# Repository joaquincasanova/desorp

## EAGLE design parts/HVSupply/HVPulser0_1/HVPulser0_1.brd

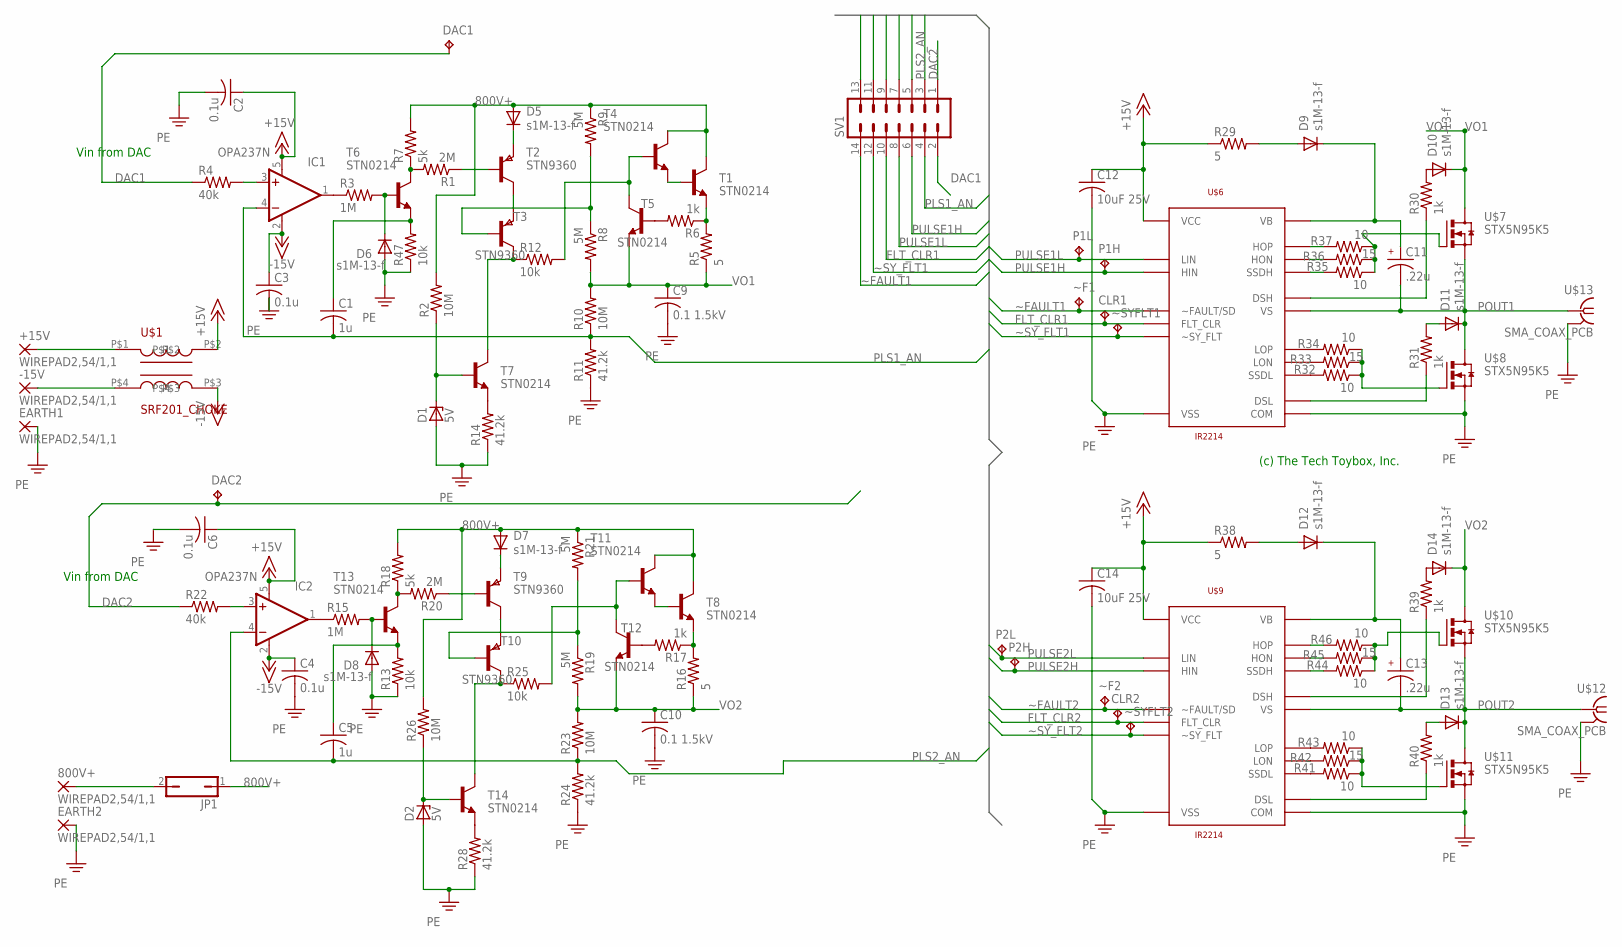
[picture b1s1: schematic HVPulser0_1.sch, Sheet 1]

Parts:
800V+: WIREPAD2,54/1,1; 2,54/1,1
+15V: WIREPAD2,54/1,1; 2,54/1,1
-15V: WIREPAD2,54/1,1; 2,54/1,1
C1, C5: 1u; C0805
C2, C3, C4, C6: 0.1u; C0805
C9, C10: 0.1 1.5kV; C2225K
C11, C13: .22u; C050-035X075; PARTNO C1608X7R1H224K080AB
C12, C14: 10uF 25V; C0805
CLR1, CLR2: TPTP10R; TP10R
D1, D2: 5V; DO41Z10
D5, D6, D7, D8, D9, D10, D11, D12, D13, D14: s1M-13-f; DO214AC
DAC1, DAC2: TPTP10R; TP10R
EARTH1, EARTH2: WIREPAD2,54/1,1; 2,54/1,1
IC1, IC2: OPA237N; SOT23-5
JP1: JP1Q; JP1
P1H, P1L, P2H, P2L: TPTP10R; TP10R
R1, R20: 2M; P0613/15
R2, R10, R23, R26: 10M; P0613/15
R3, R15: 1M; R0603
R4, R22: 40k; R0603
R5, R16: 5; P0613/15
R6, R17: 1k; P0613/15
R7, R18: 5k; R0603
R8, R9, R19, R21: 5M; P0613/15
R11, R14, R24, R28: 41.2k; P0613/15
R12, R25: 10k; R0603
R13, R47: 10k; R0805
R29, R38: 5; 0207/10
R30, R31, R39, R40: 1k; R0603
R32, R34, R35, R37, R41, R43, R44, R46: 10; R0805
R33, R36, R42, R45: 15; R0805
SV1: MA07-2
T1, T4, T5, T6, T7, T8, T11, T12, T13, T14: STN0214; SOT223
T2, T3, T9, T10: STN9360; SOT223
U$1: SRF201_CHOKE; CHOKE_BOURNES_SRF2012
U$6, U$9: IR2214; SSOP24-IR-0.65
U$7, U$8, U$10, U$11: STX5N95K5; TO220AV
U$12, U$13: SMA_COAX_PCB; SMA-COAX-V-TECONNECT
~F1, ~F2: TPTP10R; TP10R
~SYFLT1, ~SYFLT2: TPTP10R; TP10R

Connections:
800V+: D5.A, D7.A, JP1.1, R2.2, R7.2, R9.1, R18.2, R21.1, R26.2, T1.4 (C), T4.4 (C), T8.4 (C), T11.4 (C)
+15V: C2.1, C6.1, C12.1, C14.1, IC1.5 (V+), IC2.5 (V+), R29.1, R38.1, U$1.P$2, U$6.P$11 (VCC), U$9.P$11 (VCC)
+800VIN: 800V+.1, JP1.2
-15V: C3.1, C4.1, IC1.2 (V-), IC2.2 (V-), U$1.P$3
DAC1: DAC1.TP, R4.1, SV1.2
DAC2: DAC2.TP, R22.1, SV1.1
FLT_CLR1: CLR1.TP, SV1.10, U$6.P$3 (FLT_CLR)
FLT_CLR2: CLR2.TP, SV1.9, U$9.P$3 (FLT_CLR)
unnamed: -15V.1, U$1.P$4
unnamed: +15V.1, U$1.P$1
unnamed: C1.1, R47.2, T6.3 (E)
unnamed: C5.1, R13.2, T13.3 (E)
unnamed: D9.A, R29.2
unnamed: R31.1, U$6.P$12 (DSL)
unnamed: D11.A, R31.2
unnamed: R32.1, R33.1, R34.1, U$8.1 (G)
unnamed: R35.1, R36.1, R37.1, U$7.1 (G)
unnamed: R30.1, U$6.P$24 (DSH)
unnamed: D10.A, R30.2
unnamed: D12.A, R38.2
unnamed: R41.2, U$9.P$7 (SSDL)
unnamed: R42.2, U$9.P$9 (LON)
unnamed: R43.2, U$9.P$10 (LOP)
unnamed: IC1.1 (OUT), R3.1
unnamed: T2.2 (C), T2.4 (C), T3.3 (E)
unnamed: R1.1, T2.1 (B)
unnamed: D5.C, T2.3 (E)
unnamed: D6.C, R3.2, T6.1 (B)
unnamed: IC1.3 (+IN), R4.2
unnamed: R40.1, U$9.P$12 (DSL)
unnamed: R5.2, R6.1, T1.3 (E)
unnamed: T1.1 (B), T4.3 (E)
unnamed: R12.2, T4.1 (B), T5.4 (C)
unnamed: R6.2, T5.1 (B)
unnamed: R8.1, R9.2, T3.1 (B)
unnamed: R1.2, R7.1, T6.4 (C)
unnamed: R12.1, T3.2 (C), T3.4 (C), T7.4 (C)
unnamed: R14.2, T7.3 (E)
unnamed: IC2.1 (OUT), R15.1
unnamed: D1.C, R2.1, T7.1 (B)
unnamed: T9.2 (C), T9.4 (C), T10.3 (E)
unnamed: R16.2, R17.1, T8.3 (E)
unnamed: T8.1 (B), T11.3 (E)
unnamed: R17.2, T12.1 (B)
unnamed: R19.1, R21.2, T10.1 (B)
unnamed: R20.1, T9.1 (B)
unnamed: D7.C, T9.3 (E)
unnamed: R25.2, T11.1 (B), T12.4 (C)
unnamed: D8.C, R15.2, T13.1 (B)
unnamed: R18.1, R20.2, T13.4 (C)
unnamed: D13.A, R40.2
unnamed: IC2.3 (+IN), R22.2
unnamed: R25.1, T10.2 (C), T10.4 (C), T14.4 (C)
unnamed: R28.2, T14.3 (E)
unnamed: D2.C, R26.1, T14.1 (B)
unnamed: R32.2, U$6.P$7 (SSDL)
unnamed: R33.2, U$6.P$9 (LON)
unnamed: R34.2, U$6.P$10 (LOP)
unnamed: R41.1, R42.1, R43.1, U$11.1 (G)
unnamed: R44.1, R45.1, R46.1, U$10.1 (G)
unnamed: R39.1, U$9.P$24 (DSH)
unnamed: D14.A, R39.2
unnamed: R46.2, U$9.P$21 (HOP)
unnamed: R45.2, U$9.P$20 (HON)
unnamed: R44.2, U$9.P$18 (SSDH)
unnamed: R37.2, U$6.P$21 (HOP)
unnamed: R36.2, U$6.P$20 (HON)
unnamed: R35.2, U$6.P$18 (SSDH)
PE: C2.2, C3.2, C4.2, C6.2, C9.2, C10.2, C12.2, C14.2, D1.A, D2.A, D6.A, D8.A, EARTH1.1, EARTH2.1, R11.1, R13.1, R14.1, R24.1, R28.1, R47.1, U$6.P$6 (VSS), U$6.P$8 (COM), U$8.3 (S), U$9.P$6 (VSS), U$9.P$8 (COM), U$11.3 (S), U$12.2, U$12.3 (2), U$12.4 (2), U$12.5 (2), U$13.2, U$13.3 (2), U$13.4 (2), U$13.5 (2)
PLS1_AN: C1.2, IC1.4 (-IN), R10.1, R11.2, SV1.4
PLS2_AN: C5.2, IC2.4 (-IN), R23.1, R24.2, SV1.3
POUT1: C11.2, D11.C, U$6.P$19 (VS), U$7.3 (S), U$8.2 (D), U$13.1
POUT2: C13.2, D13.C, U$9.P$19 (VS), U$10.3 (S), U$11.2 (D), U$12.1
PULSE1H: P1H.TP, SV1.6, U$6.P$1 (HIN)
PULSE1L: P1L.TP, SV1.8, U$6.P$2 (LIN)
PULSE2H: P2H.TP, SV1.13, U$9.P$1 (HIN)
PULSE2L: P2L.TP, SV1.11, U$9.P$2 (LIN)
VB3: C11.1, D9.C, U$6.P$23 (VB)
VB4: C13.1, D12.C, U$9.P$23 (VB)
VO1: C9.1, D10.C, R5.1, R8.2, R10.2, T5.3 (E), U$7.2 (D)
VO2: C10.1, D14.C, R16.1, R19.2, R23.2, T12.3 (E), U$10.2 (D)
~FAULT1: SV1.14, U$6.P$5 (~FAULT/SD), ~F1.TP
~FAULT2: SV1.5, U$9.P$5 (~FAULT/SD), ~F2.TP
~SY_FLT1: SV1.12, U$6.P$4 (~SY_FLT), ~SYFLT1.TP
~SY_FLT2: SV1.7, U$9.P$4 (~SY_FLT), ~SYFLT2.TP

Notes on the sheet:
Vin from DAC
(c) The Tech Toybox, Inc.

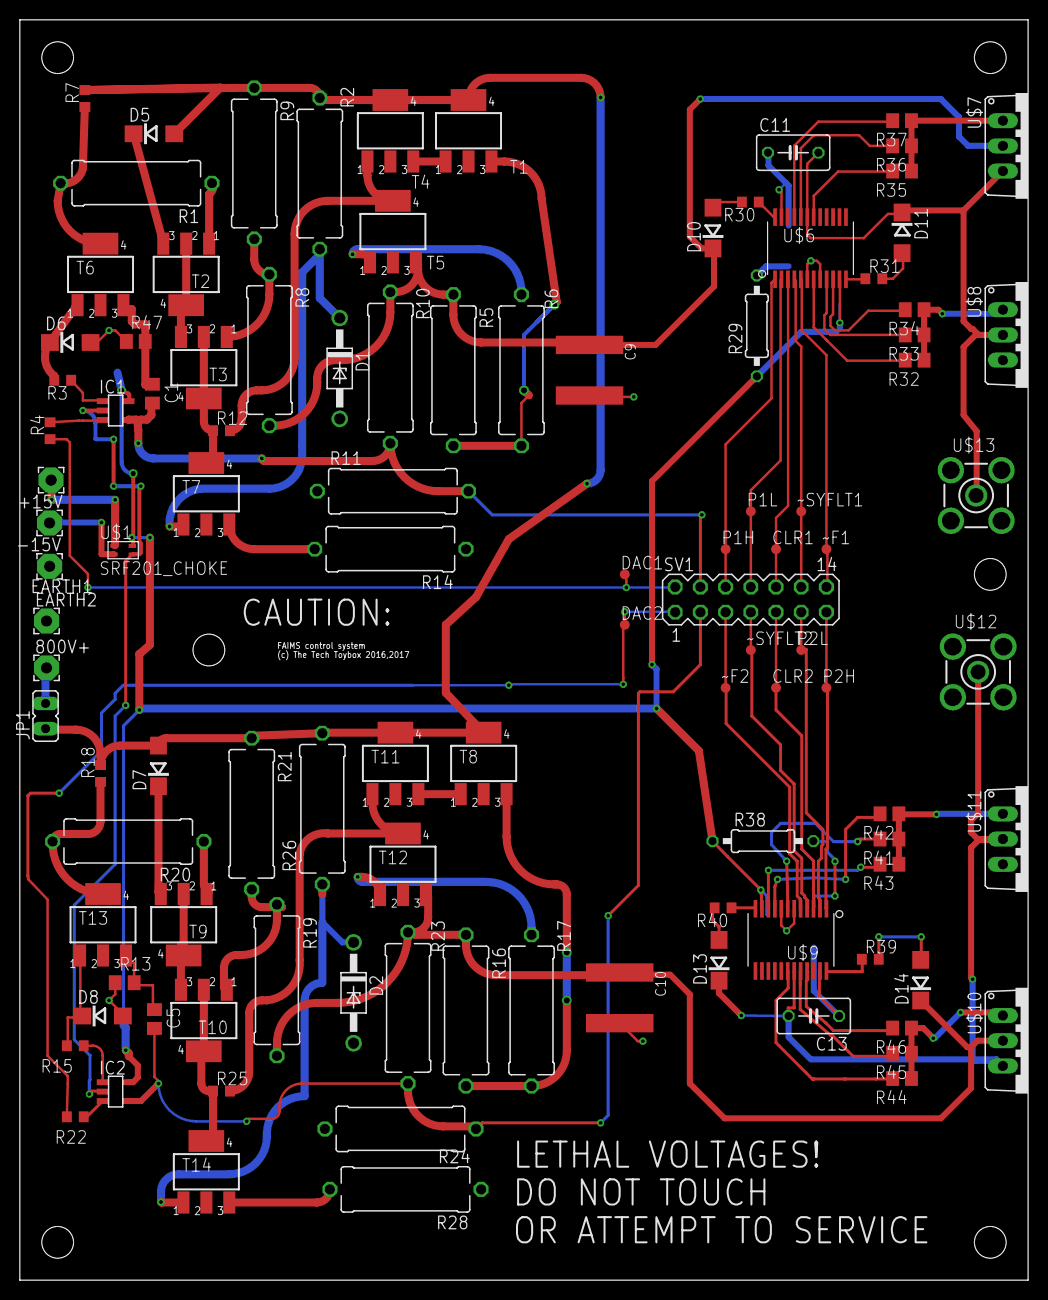
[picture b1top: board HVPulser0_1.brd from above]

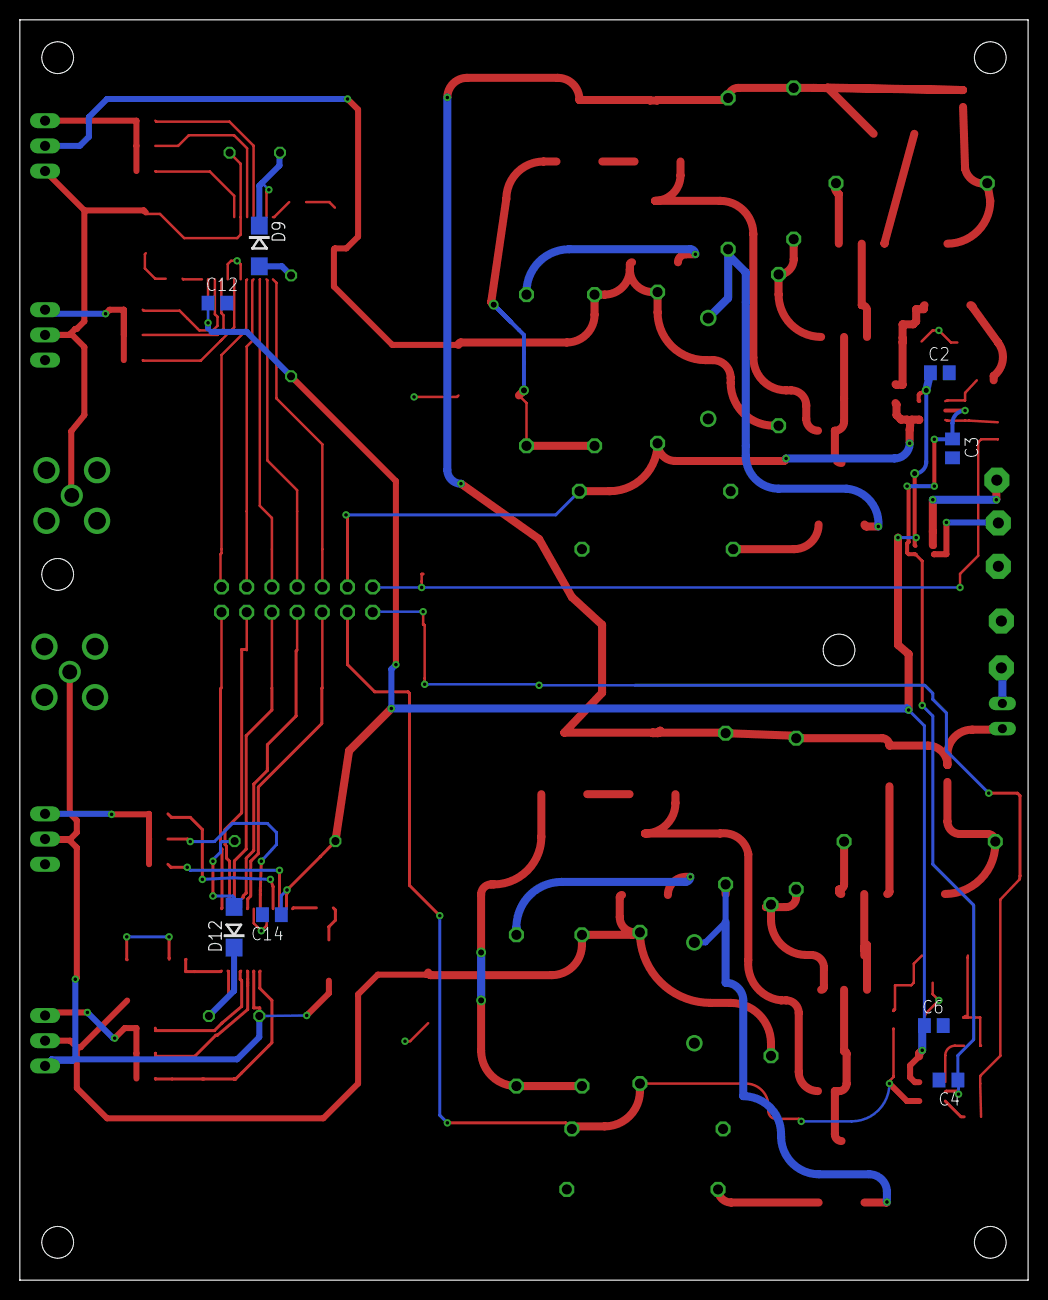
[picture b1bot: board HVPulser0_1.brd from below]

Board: 2 copper layers, 101.6 x 127.0 mm, 114 parts (8 on the bottom side), 85 nets.

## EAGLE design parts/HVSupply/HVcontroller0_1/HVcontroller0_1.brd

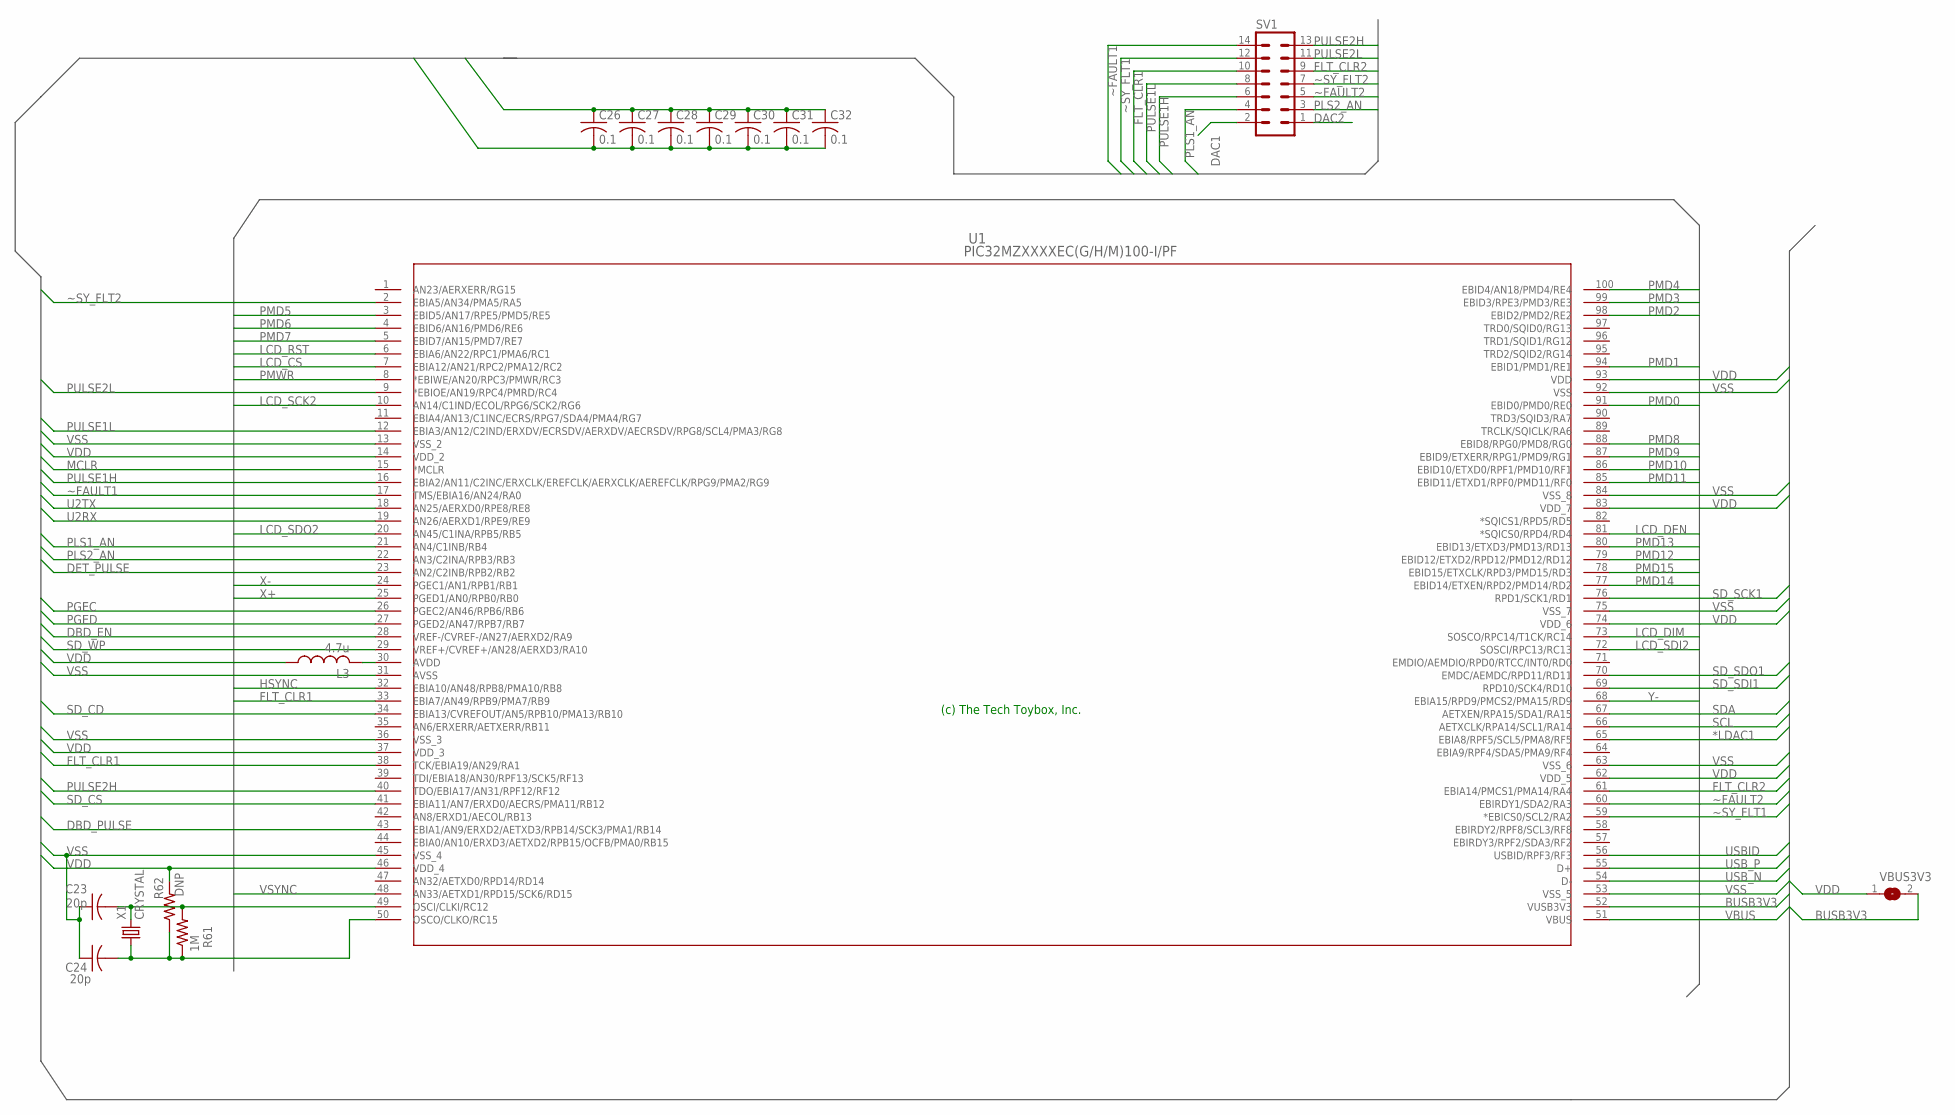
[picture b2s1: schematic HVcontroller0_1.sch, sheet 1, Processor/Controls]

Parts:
C23, C24: 20p; C0402
C26, C27, C28, C29, C30, C31, C32: 0.1; C0603
L3: 4.7u; L2012C
R61: 1M; R0402
R62: DNP; R0402
SV1: MA07-2
U1: PIC32MZXXXXEC(G/H/M)100-I/PF; TQFP100_14X14MC
VBUS3V3: SJ
X1: CRYSTAL; ABM

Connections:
*LDAC1: U1.65 (EBIA8/RPF5/SCL5/PMA8/RF5); also elsewhere on the board
BUSB3V3: U1.52 (VUSB3V3), VBUS3V3.2
DAC1: SV1.2; also elsewhere on the board
DAC2: SV1.1; also elsewhere on the board
DBD_EN: U1.28 (VREF-/CVREF-/AN27/AERXD2/RA9)
DBD_PULSE: U1.43 (EBIA1/AN9/ERXD2/AETXD3/RPB14/SCK3/PMA1/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)
DET_PULSE: U1.23 (AN2/C2INB/RPB2/RB2); also elsewhere on the board
FLT_CLR1: SV1.10, U1.38 (TCK/EBIA19/AN29/RA1)
FLT_CLR2: SV1.9, U1.61 (EBIA14/PMCS1/PMA14/RA4)
HSYNC: U1.32 (EBIA10/AN48/RPB8/PMA10/RB8)
LCD_CS: U1.7 (EBIA12/AN21/RPC2/PMA12/RC2)
LCD_DEN: U1.81 (*SQICS0/RPD4/RD4)
LCD_DIM: U1.73 (SOSCO/RPC14/T1CK/RC14)
LCD_RST: U1.6 (EBIA6/AN22/RPC1/PMA6/RC1)
LCD_SCK2: U1.10 (AN14/C1IND/ECOL/RPG6/SCK2/RG6)
LCD_SDI2: U1.72 (SOSCI/RPC13/RC13)
LCD_SDO2: U1.20 (AN45/C1INA/RPB5/RB5)
MCLR: U1.15 (*MCLR); also elsewhere on the board
unnamed: L3.2, U1.30 (AVDD)
unnamed: C23.2, R61.2, U1.49 (OSCI/CLKI/RC12), X1.P$2 (2)
unnamed: C24.2, R61.1, R62.1, U1.50 (OSCO/CLKO/RC15), X1.P$1 (1)
PGEC: U1.26 (PGEC2/AN46/RPB6/RB6); also elsewhere on the board
PGED: U1.27 (PGED2/AN47/RPB7/RB7); also elsewhere on the board
PLS1_AN: SV1.4, U1.21 (AN4/C1INB/RB4)
PLS2_AN: SV1.3, U1.22 (AN3/C2INA/RPB3/RB3)
PMD0: U1.91 (EBID0/PMD0/RE0)
PMD1: U1.94 (EBID1/PMD1/RE1)
PMD2: U1.98 (EBID2/PMD2/RE2)
PMD3: U1.99 (EBID3/RPE3/PMD3/RE3)
PMD4: U1.100 (EBID4/AN18/PMD4/RE4)
PMD5: U1.3 (EBID5/AN17/RPE5/PMD5/RE5)
PMD6: U1.4 (EBID6/AN16/PMD6/RE6)
PMD7: U1.5 (EBID7/AN15/PMD7/RE7)
PMD8: U1.88 (EBID8/RPG0/PMD8/RG0)
PMD9: U1.87 (EBID9/ETXERR/RPG1/PMD9/RG1)
PMD10: U1.86 (EBID10/ETXD0/RPF1/PMD10/RF1)
PMD11: U1.85 (EBID11/ETXD1/RPF0/PMD11/RF0)
PMD12: U1.79 (EBID12/ETXD2/RPD12/PMD12/RD12)
PMD13: U1.80 (EBID13/ETXD3/PMD13/RD13)
PMD14: U1.77 (EBID14/ETXEN/RPD2/PMD14/RD2)
PMD15: U1.78 (EBID15/ETXCLK/RPD3/PMD15/RD3)
PMWR: U1.8 (*EBIWE/AN20/RPC3/PMWR/RC3)
PULSE1H: SV1.6, U1.16 (EBIA2/AN11/C2INC/ERXCLK/EREFCLK/AERXCLK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)
PULSE1L: SV1.8, U1.12 (EBIA3/AN12/C2IND/ERXDV/ECRSDV/AERXDV/AE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)
PULSE2H: SV1.13, U1.40 (TDO/EBIA17/AN31/RPF12/RF12)
PULSE2L: SV1.11, U1.9 (*EBIOE/AN19/RPC4/PMRD/RC4)
SCL: U1.66 (AETXCLK/RPA14/SCL1/RA14); also elsewhere on the board
SDA: U1.67 (AETXEN/RPA15/SDA1/RA15); also elsewhere on the board
SD_CD: U1.34 (EBIA13/CVREFOUT/AN5/RPB10/PMA13/RB10); also elsewhere on the board
SD_CS: U1.41 (EBIA11/AN7/ERXD0/AECRS/PMA11/RB12); also elsewhere on the board
SD_SCK1: U1.76 (RPD1/SCK1/RD1); also elsewhere on the board
SD_SDI1: U1.69 (RPD10/SCK4/RD10); also elsewhere on the board
SD_SDO1: U1.70 (EMDC/AEMDC/RPD11/RD11); also elsewhere on the board
SD_WP: U1.29 (VREF+/CVREF+/AN28/AERXD3/RA10); also elsewhere on the board
U2RX: U1.19 (AN26/AERXD1/RPE9/RE9); also elsewhere on the board
U2TX: U1.18 (AN25/AERXD0/RPE8/RE8); also elsewhere on the board
USBID: U1.56 (USBID/RPF3/RF3); also elsewhere on the board
USB_N: U1.54 (D-); also elsewhere on the board
USB_P: U1.55 (D+); also elsewhere on the board
VBUS: U1.51 (VBUS); also elsewhere on the board
VDD: C26.1, C27.1, C28.1, C29.1, C30.1, C31.1, C32.1, L3.1, R62.2, U1.14 (VDD_2), U1.37 (VDD_3), U1.46 (VDD_4), U1.62 (VDD_5), U1.74 (VDD_6), U1.83 (VDD_7), U1.93 (VDD), VBUS3V3.1; also elsewhere on the board
VSS: C23.1, C24.1, C26.2, C27.2, C28.2, C29.2, C30.2, C31.2, C32.2, U1.13 (VSS_2), U1.31 (AVSS), U1.36 (VSS_3), U1.45 (VSS_4), U1.53 (VSS_5), U1.63 (VSS_6), U1.75 (VSS_7), U1.84 (VSS_8), U1.92 (VSS); also elsewhere on the board
VSYNC: U1.48 (AN33/AETXD1/RPD15/SCK6/RD15)
X+: U1.25 (PGED1/AN0/RPB0/RB0)
X-: U1.24 (PGEC1/AN1/RPB1/RB1)
Y+: U1.33 (EBIA7/AN49/RPB9/PMA7/RB9)
Y-: U1.68 (EBIA15/RPD9/PMCS2/PMA15/RD9)
~FAULT1: SV1.14, U1.17 (TMS/EBIA16/AN24/RA0)
~FAULT2: SV1.5, U1.60 (EBIRDY1/SDA2/RA3)
~SY_FLT1: SV1.12, U1.59 (*EBICS0/SCL2/RA2)
~SY_FLT2: SV1.7, U1.2 (EBIA5/AN34/PMA5/RA5)

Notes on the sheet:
(c) The Tech Toybox, Inc.

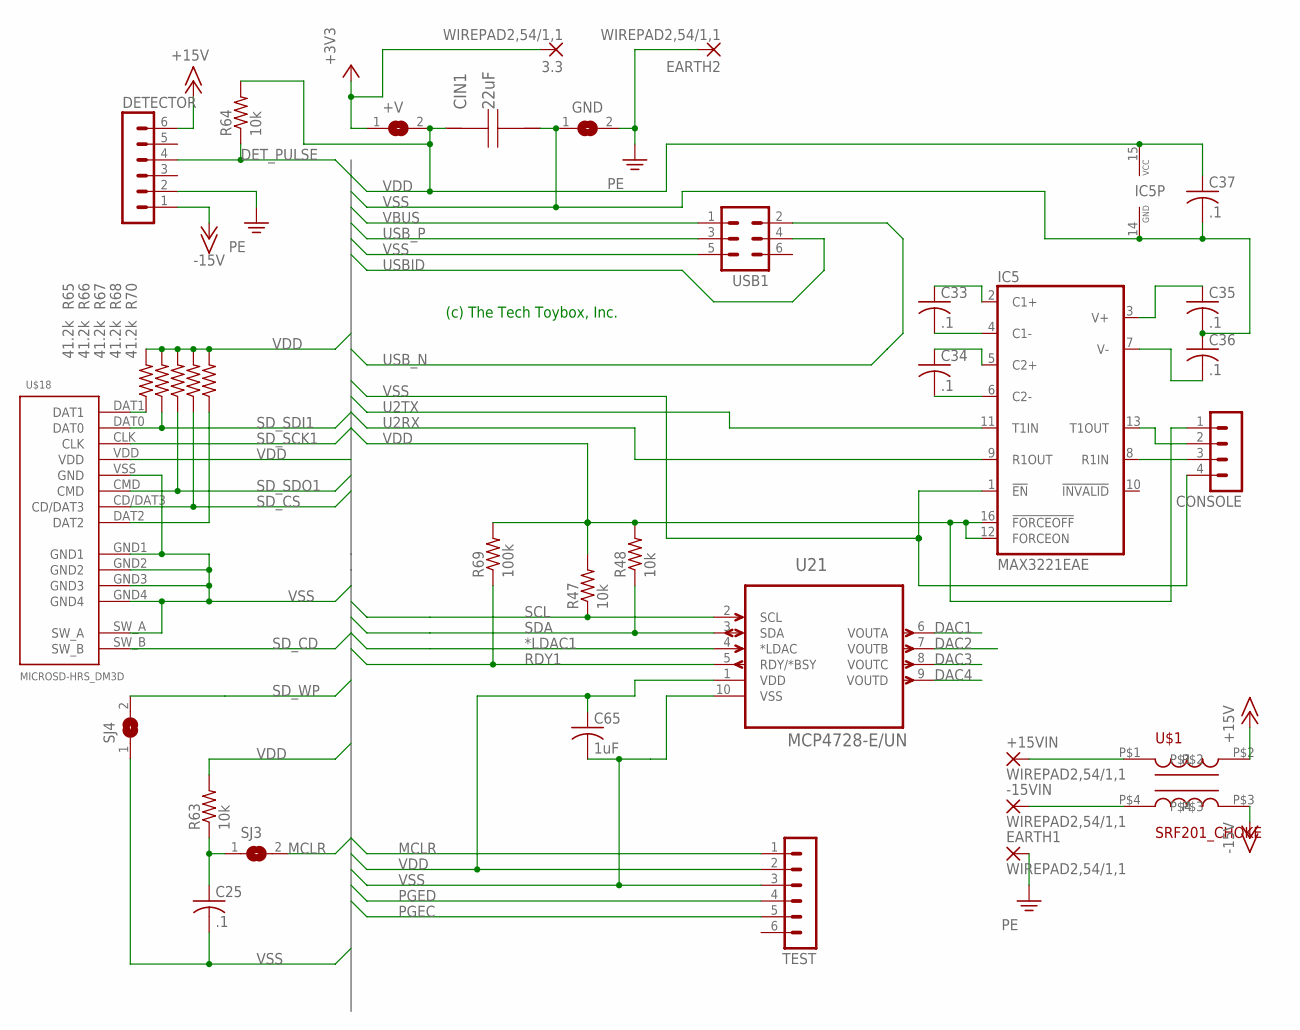
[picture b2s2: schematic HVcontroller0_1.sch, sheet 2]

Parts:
3.3: WIREPAD2,54/1,1; 2,54/1,1
+15VIN: WIREPAD2,54/1,1; 2,54/1,1
+V: SJW
-15VIN: WIREPAD2,54/1,1; 2,54/1,1
C25, C33, C34, C35, C36, C37: .1; C0402
C65: 1uF; C0402
CIN1: 22uF; 1210
CONSOLE: MA04-1
DETECTOR: MA06-1
EARTH1, EARTH2: WIREPAD2,54/1,1; 2,54/1,1
GND: SJW
IC5: MAX3221EAE; SSOP16
R47, R48, R63, R64: 10k; R0805
R65, R66, R67, R68, R70: 41.2k; R0603
R69: 100k; R0805
SJ3, SJ4: SJ
TEST: MA06-1
U21: MCP4728-E/UN; SOP50P490X110-10N
U$1: SRF201_CHOKE; CHOKE_BOURNES_SRF2012
U$18: MICROSD-HRS_DM3D; DM3D
USB1: MA03-2

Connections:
*LDAC1: U21.4 (*LDAC); also elsewhere on the board
+3V3: 3.3.1, +V.1
+15V: DETECTOR.6, U$1.P$2
-15V: DETECTOR.1, U$1.P$3
DAC1: U21.6 (VOUTA); also elsewhere on the board
DAC2: U21.7 (VOUTB); also elsewhere on the board
DAC3: U21.8 (VOUTC)
DAC4: U21.9 (VOUTD)
DET_PULSE: DETECTOR.4, R64.1; also elsewhere on the board
MCLR: SJ3.2, TEST.1; also elsewhere on the board
unnamed: -15VIN.1, U$1.P$4
unnamed: +15VIN.1, U$1.P$1
unnamed: R65.1, U$18.DAT1
unnamed: R70.1, U$18.DAT2
unnamed: C33.1, IC5.2 (C1+)
unnamed: C25.1, R63.1, SJ3.1
unnamed: C33.2, IC5.4 (C1-)
unnamed: C34.1, IC5.5 (C2+)
unnamed: C34.2, IC5.6 (C2-)
unnamed: C35.1, IC5.3 (V+)
unnamed: C36.2, IC5.7 (V-)
unnamed: CONSOLE.2, IC5.13 (T1OUT)
unnamed: CONSOLE.3, IC5.8 (R1IN)
PE: DETECTOR.2, EARTH1.1, EARTH2.1, GND.2
PGEC: TEST.5; also elsewhere on the board
PGED: TEST.4; also elsewhere on the board
RDY1: R69.1, U21.5 (RDY/*BSY)
SCL: R47.1, U21.2 (SCL); also elsewhere on the board
SDA: R48.1, U21.3 (SDA); also elsewhere on the board
SD_CD: U$18.SW_B; also elsewhere on the board
SD_CS: R68.1, U$18.CD/DAT3; also elsewhere on the board
SD_SCK1: U$18.CLK; also elsewhere on the board
SD_SDI1: R66.1, U$18.DAT0; also elsewhere on the board
SD_SDO1: R67.1, U$18.CMD; also elsewhere on the board
SD_WP: SJ4.2; also elsewhere on the board
U2RX: IC5.9 (R1OUT); also elsewhere on the board
U2TX: IC5.11 (T1IN); also elsewhere on the board
USBID: USB1.4; also elsewhere on the board
USB_N: USB1.2; also elsewhere on the board
USB_P: USB1.3; also elsewhere on the board
VBUS: USB1.1; also elsewhere on the board
VDD: +V.2, C37.1, C65.1, CIN1.1, CONSOLE.1, IC5.12 (FORCEON), IC5.15 (VCC), IC5.16 (!FORCEOFF), R47.2, R48.2, R63.2, R64.2, R65.2, R66.2, R67.2, R68.2, R69.2, R70.2, TEST.2, U21.1 (VDD), U$18.VDD; also elsewhere on the board
VSS: C25.2, C35.2, C36.1, C37.2, C65.2, CIN1.2, CONSOLE.4, GND.1, IC5.1 (!EN), IC5.14 (GND), SJ4.1, TEST.3, U21.10 (VSS), U$18.GND1, U$18.GND2, U$18.GND3, U$18.GND4, U$18.SW_A, U$18.VSS (GND), USB1.5; also elsewhere on the board

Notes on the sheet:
(c) The Tech Toybox, Inc.

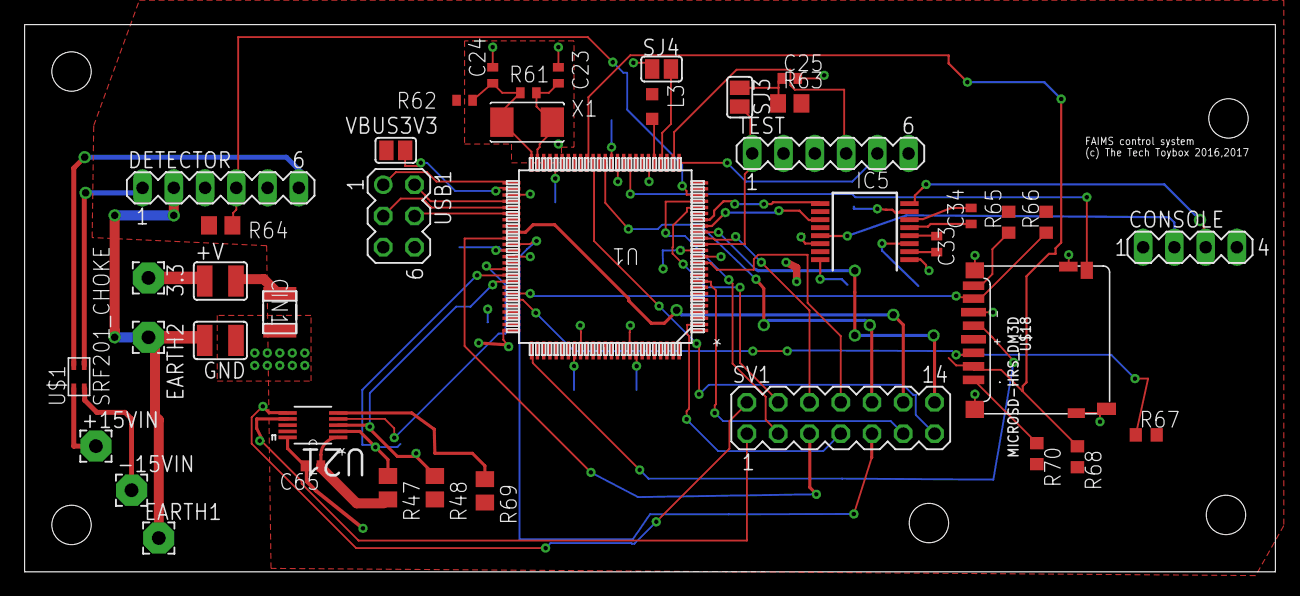
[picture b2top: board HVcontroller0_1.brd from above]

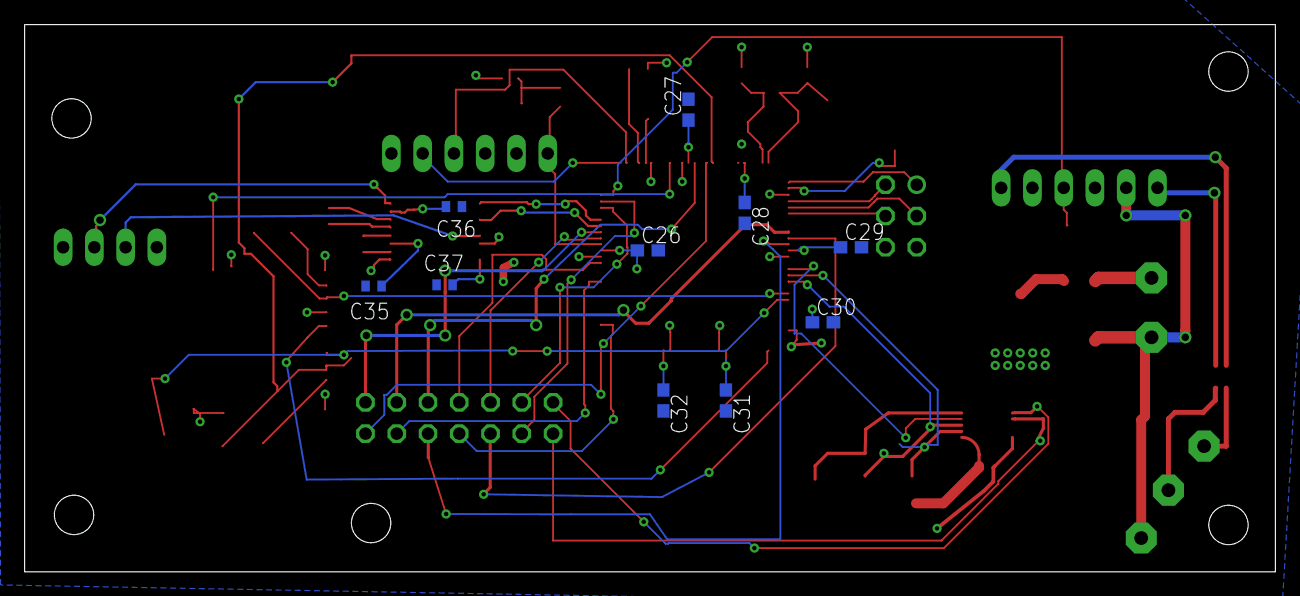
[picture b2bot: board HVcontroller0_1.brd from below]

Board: 2 copper layers, 101.6 x 44.5 mm, 51 parts (10 on the bottom side), 57 nets.

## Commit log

2017-06-06 first
2017-06-07 npt threads
2017-06-07 drill size
2017-06-21 f and s
2017-07-06 lens
2017-07-11 drawing updates
2017-08-05 invoices
2017-08-08 final?
